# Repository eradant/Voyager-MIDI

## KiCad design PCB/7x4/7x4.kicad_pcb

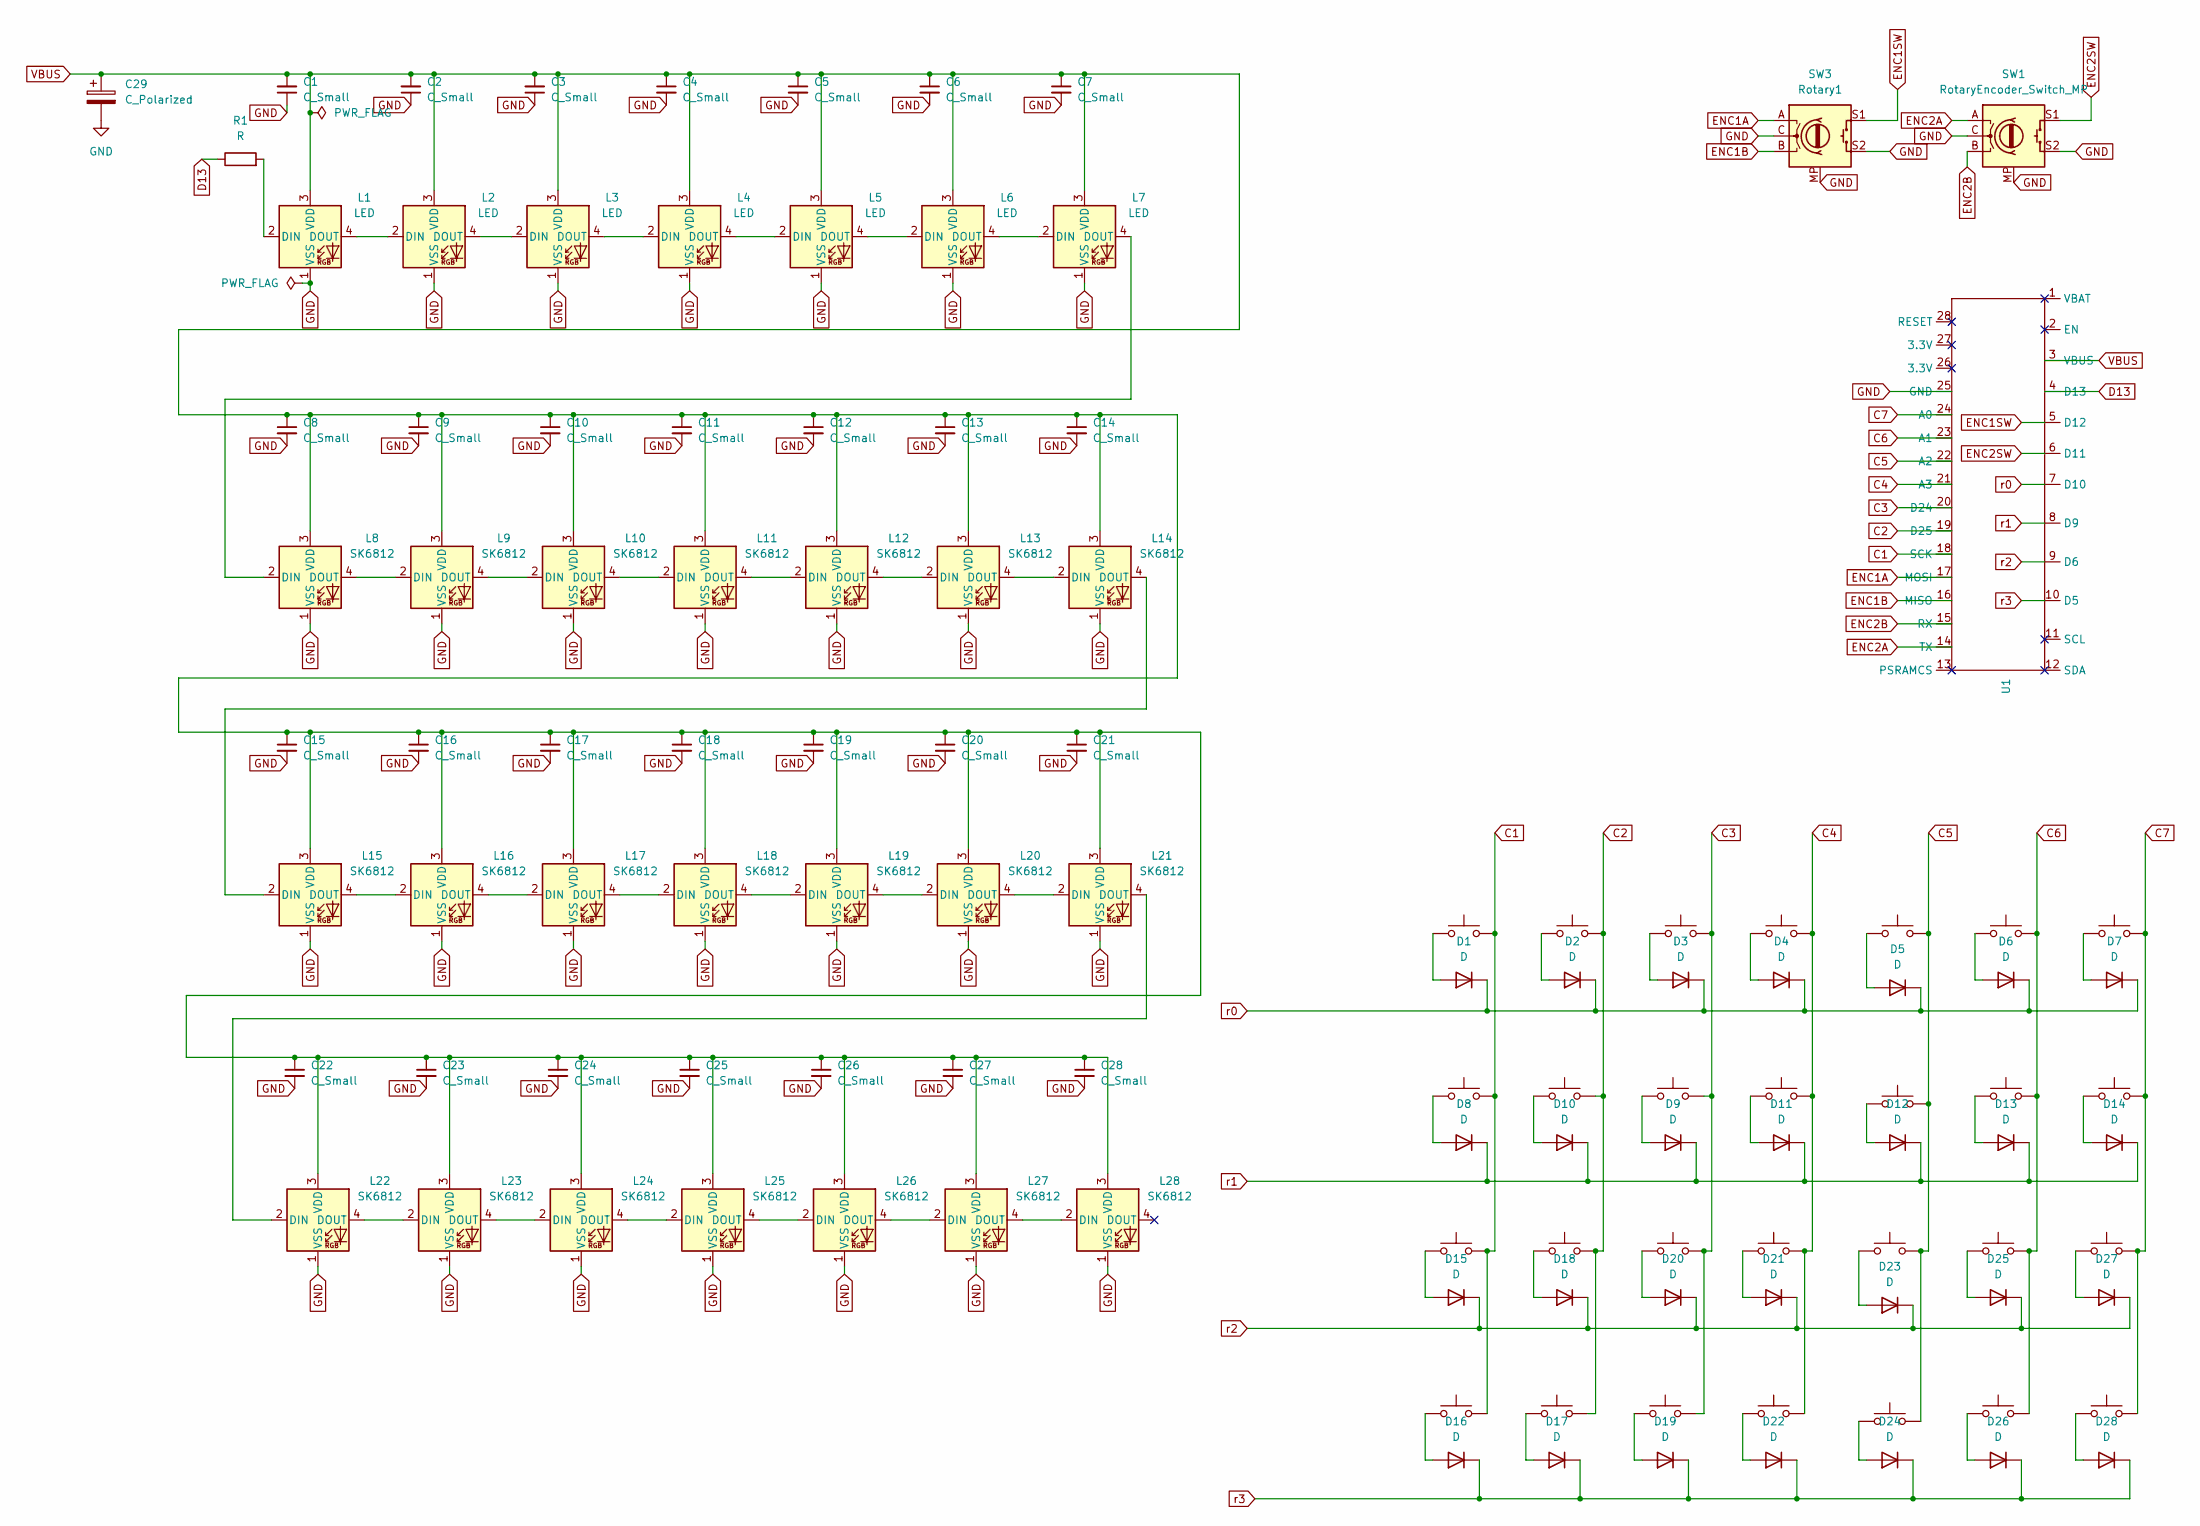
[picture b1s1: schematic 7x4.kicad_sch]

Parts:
C1, C2, C3, C4, C5, C6, C7, C8, C9, C10, C11, C12, C13, C14, C15, C16, C17, C18, C19, C20, C21, C22, C23, C24, C25, C26, C27, C28: C_Small; C_0805_2012Metric
C29: C_Polarized; CP_Elec_6.3x7.7
D1, D2, D3, D4, D5, D6, D7, D8, D9, D10, D11, D12, D13, D14, D15, D16, D17, D18, D19, D20, D21, D22, D23, D24, D25, D26, D27, D28: D; D_SOD-123
F1, F2, F3, F4, F5, F6, F7: SW_Push; SW_Cherry_MX_1.00u_PCB
K2: SW_Cherry_MX_1.00u_PCB
L1, L2, L3, L4, L5, L6, L7: LED; MX_SK6812MINI-E_REV
L8, L9, L10, L11, L12, L13, L14, L15, L16, L17, L18, L19, L20, L21, L22, L23, L24, L25, L26, L27, L28: SK6812; MX_SK6812MINI-E_REV
O1-1, O1-2, O1-3: SW_Cherry_MX_1.00u_PCB
O1-4, O1-5, O1-6, O1-7: SW_Push; SW_Cherry_MX_1.00u_PCB
R1: R; R_0805_2012Metric
SW1: RotaryEncoder_Switch_MP; RotaryEncoder_Alps_EC11E-Switch_Vertical_H20mm_MountingHoles
SW3: Rotary1; RotaryEncoder_Alps_EC11E-Switch_Vertical_H20mm_MountingHoles
SWK3, SWK4, SWK5, SWK6, SWK7, SWK8, SWK9, SWK10, SWK11, SWK12, SWK13, SWK14: SW_Cherry_MX_1.00u_PCB
U1: Untitled
o3-3: SW_Cherry_MX_1.00u_PCB

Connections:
C1: F1.2, O1-1.2, SWK8.2, U1.18 (SCK), o3-3.2
C2: F2.2, K2.2, O1-2.2, SWK9.2, U1.19 (D25)
C3: F3.2, O1-3.2, SWK3.2, SWK10.2, U1.20 (D24)
C4: F4.2, O1-4.2, SWK4.2, SWK11.2, U1.21 (A3)
C5: F5.2, O1-5.2, SWK5.2, SWK12.2, U1.22 (A2)
C6: F6.2, O1-6.2, SWK6.2, SWK13.2, U1.23 (A1)
C7: F7.2, O1-7.2, SWK7.2, SWK14.2, U1.24 (A0)
D13: R1.1, U1.4 (D13)
ENC1A: SW3.A, U1.17 (MOSI)
ENC1B: SW3.B, U1.16 (MISO)
ENC1SW: SW3.S1, U1.5 (D12)
ENC2A: SW1.A, U1.14 (TX)
ENC2B: SW1.B, U1.15 (RX)
ENC2SW: SW1.S1, U1.6 (D11)
GND: C1.1, C2.1, C3.1, C4.2, C5.2, C6.2, C7.2, C8.2, C9.2, C10.2, C11.2, C12.2, C13.2, C14.2, C15.2, C16.2, C17.2, C18.2, C19.2, C20.2, C21.2, C22.2, C23.2, C24.2, C25.2, C26.2, C27.2, C28.2, C29.2, L1.1 (VSS), L2.1 (VSS), L3.1 (VSS), L4.1 (VSS), L5.1 (VSS), L6.1 (VSS), L7.1 (VSS), L8.1 (VSS), L9.1 (VSS), L10.1 (VSS), L11.1 (VSS), L12.1 (VSS), L13.1 (VSS), L14.1 (VSS), L15.1 (VSS), L16.1 (VSS), L17.1 (VSS), L18.1 (VSS), L19.1 (VSS), L20.1 (VSS), L21.1 (VSS), L22.1 (VSS), L23.1 (VSS), L24.1 (VSS), L25.1 (VSS), L26.1 (VSS), L27.1 (VSS), L28.1 (VSS), SW1.C, SW1.MP, SW1.S2, SW3.C, SW3.MP, SW3.S2, U1.25 (GND)
unnamed: D1.2 (A), o3-3.1
unnamed: D2.2 (A), K2.1
unnamed: D3.2 (A), SWK3.1
unnamed: D4.2 (A), SWK4.1
unnamed: D5.2 (A), SWK5.1
unnamed: D6.2 (A), SWK6.1
unnamed: D7.2 (A), SWK7.1
unnamed: D8.2 (A), SWK8.1
unnamed: D9.2 (A), SWK10.1
unnamed: D10.2 (A), SWK9.1
unnamed: D11.2 (A), SWK11.1
unnamed: D12.2 (A), SWK12.1
unnamed: D13.2 (A), SWK13.1
unnamed: D14.2 (A), SWK14.1
unnamed: D15.2 (A), O1-1.1
unnamed: D16.2 (A), F1.1
unnamed: D17.2 (A), F2.1
unnamed: D18.2 (A), O1-2.1
unnamed: D19.2 (A), F3.1
unnamed: D20.2 (A), O1-3.1
unnamed: D21.2 (A), O1-4.1
unnamed: D22.2 (A), F4.1
unnamed: D23.2 (A), O1-5.1
unnamed: D24.2 (A), F5.1
unnamed: D25.2 (A), O1-6.1
unnamed: D26.2 (A), F6.1
unnamed: D27.2 (A), O1-7.1
unnamed: D28.2 (A), F7.1
unnamed: L1.2 (DIN), R1.2
unnamed: L1.4 (DOUT), L2.2 (DIN)
unnamed: L2.4 (DOUT), L3.2 (DIN)
unnamed: L3.4 (DOUT), L4.2 (DIN)
unnamed: L4.4 (DOUT), L5.2 (DIN)
unnamed: L5.4 (DOUT), L6.2 (DIN)
unnamed: L6.4 (DOUT), L7.2 (DIN)
unnamed: L7.4 (DOUT), L8.2 (DIN)
unnamed: L8.4 (DOUT), L9.2 (DIN)
unnamed: L9.4 (DOUT), L10.2 (DIN)
unnamed: L10.4 (DOUT), L11.2 (DIN)
unnamed: L11.4 (DOUT), L12.2 (DIN)
unnamed: L12.4 (DOUT), L13.2 (DIN)
unnamed: L13.4 (DOUT), L14.2 (DIN)
unnamed: L14.4 (DOUT), L15.2 (DIN)
unnamed: L15.4 (DOUT), L16.2 (DIN)
unnamed: L16.4 (DOUT), L17.2 (DIN)
unnamed: L17.4 (DOUT), L18.2 (DIN)
unnamed: L18.4 (DOUT), L19.2 (DIN)
unnamed: L19.4 (DOUT), L20.2 (DIN)
unnamed: L20.4 (DOUT), L21.2 (DIN)
unnamed: L21.4 (DOUT), L22.2 (DIN)
unnamed: L22.4 (DOUT), L23.2 (DIN)
unnamed: L23.4 (DOUT), L24.2 (DIN)
unnamed: L24.4 (DOUT), L25.2 (DIN)
unnamed: L25.4 (DOUT), L26.2 (DIN)
unnamed: L26.4 (DOUT), L27.2 (DIN)
unnamed: L27.4 (DOUT), L28.2 (DIN)
VBUS: C1.2, C2.2, C3.2, C4.1, C5.1, C6.1, C7.1, C8.1, C9.1, C10.1, C11.1, C12.1, C13.1, C14.1, C15.1, C16.1, C17.1, C18.1, C19.1, C20.1, C21.1, C22.1, C23.1, C24.1, C25.1, C26.1, C27.1, C28.1, C29.1, L1.3 (VDD), L2.3 (VDD), L3.3 (VDD), L4.3 (VDD), L5.3 (VDD), L6.3 (VDD), L7.3 (VDD), L8.3 (VDD), L9.3 (VDD), L10.3 (VDD), L11.3 (VDD), L12.3 (VDD), L13.3 (VDD), L14.3 (VDD), L15.3 (VDD), L16.3 (VDD), L17.3 (VDD), L18.3 (VDD), L19.3 (VDD), L20.3 (VDD), L21.3 (VDD), L22.3 (VDD), L23.3 (VDD), L24.3 (VDD), L25.3 (VDD), L26.3 (VDD), L27.3 (VDD), L28.3 (VDD), U1.3 (VBUS)
r0: D1.1 (K), D2.1 (K), D3.1 (K), D4.1 (K), D5.1 (K), D6.1 (K), D7.1 (K), U1.7 (D10)
r1: D8.1 (K), D9.1 (K), D10.1 (K), D11.1 (K), D12.1 (K), D13.1 (K), D14.1 (K), U1.8 (D9)
r2: D15.1 (K), D18.1 (K), D20.1 (K), D21.1 (K), D23.1 (K), D25.1 (K), D27.1 (K), U1.9 (D6)
r3: D16.1 (K), D17.1 (K), D19.1 (K), D22.1 (K), D24.1 (K), D26.1 (K), D28.1 (K), U1.10 (D5)

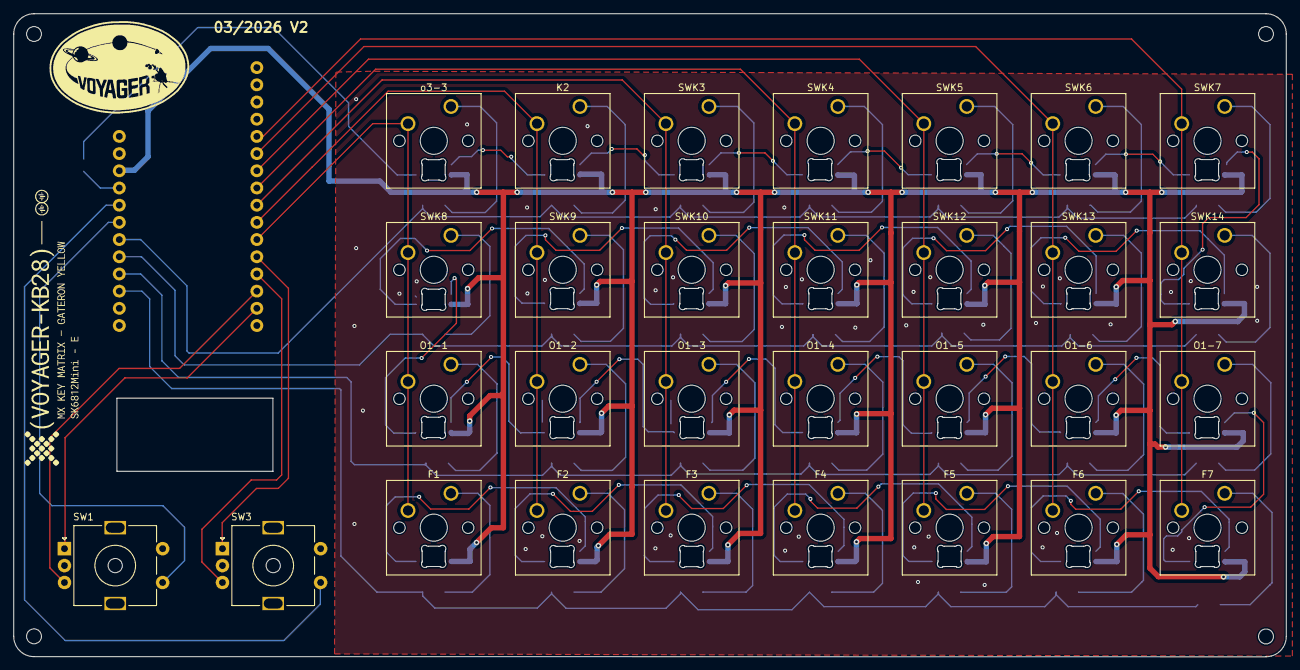
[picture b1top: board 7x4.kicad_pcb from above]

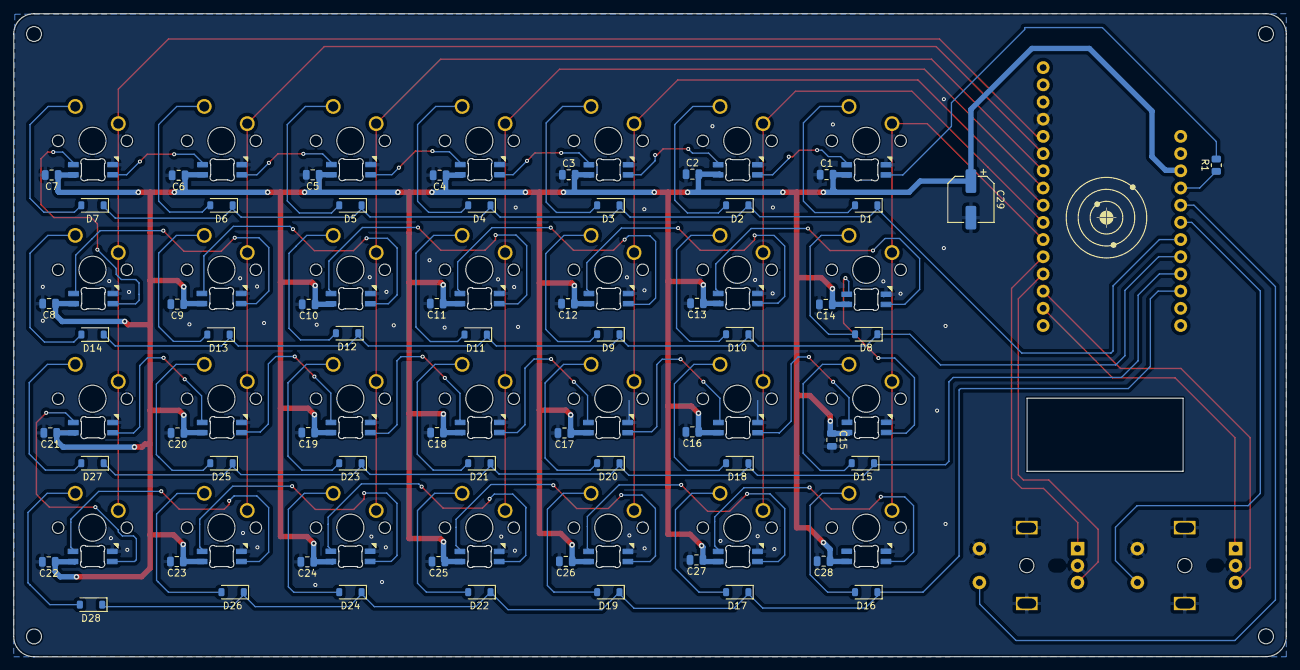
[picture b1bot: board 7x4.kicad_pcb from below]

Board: 2 copper layers, 187.9 x 95.0 mm, 117 parts (59 on the bottom side), 76 nets.

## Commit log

2026-05-15 initial
    initial upload
2026-05-16 configurator
    configurator
2026-05-16 Update index.html
    updates to config
2026-05-16 Update index.html
    color updates
2026-05-16 Update index.html
    updates
2026-05-16 Update index.html
    fixes
2026-05-16 Update index.html
    visualizer
2026-05-16 Update index.html
    f
2026-05-16 Update index.html
    encoder support
2026-05-16 updates
    updates
2026-05-16 Update index.html
    theme
2026-05-20 Update index.html
    template layers
